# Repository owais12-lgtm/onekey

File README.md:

# One key macropad! 
its a macropad with one key and one encoder powered by a XIAO!

# Features
- Modular Design
- RP2040
- Plug-and-Play
# PCB

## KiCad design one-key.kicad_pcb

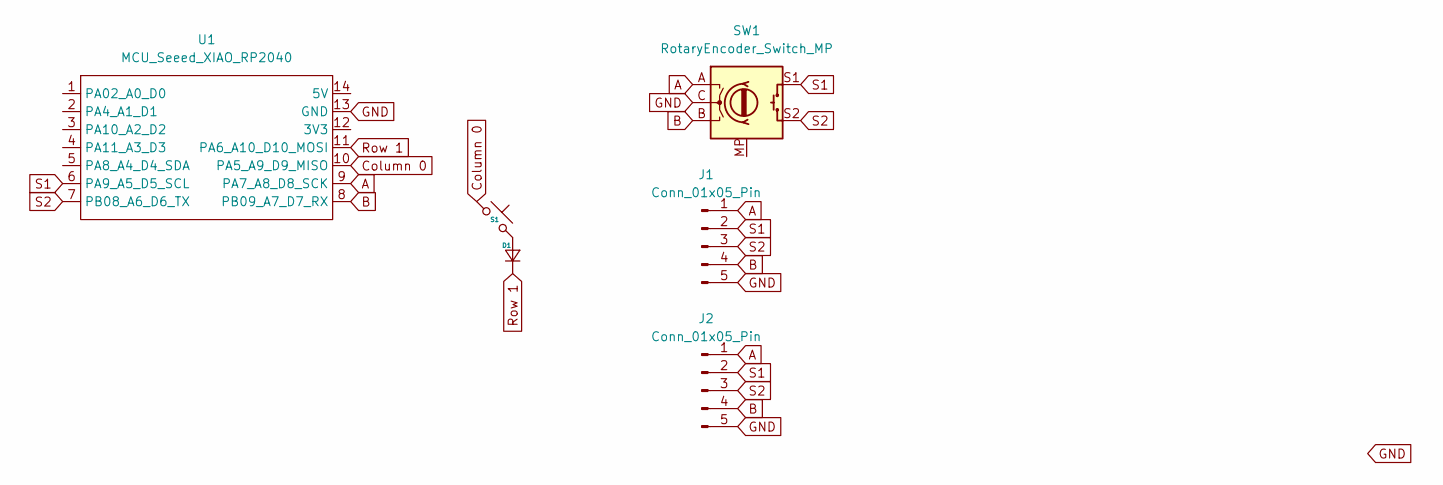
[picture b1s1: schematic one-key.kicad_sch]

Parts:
D1: Diode_DO-35
J1, J2: Conn_01x05_Pin; JST_EH_B5B-EH-A_1x05_P2.50mm_Vertical
S1: MX_PCB_1.00u
SW1: RotaryEncoder_Switch_MP; RotaryEncoder_Alps_EC11E-Switch_Vertical_H20mm
U1: MCU_Seeed_XIAO_RP2040; Seeed_XIAO_RP2040

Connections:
A: J1.1, J2.1, SW1.A, U1.9 (PA7_A8_D8_SCK)
B: J1.4, J2.4, SW1.B, U1.8 (PB09_A7_D7_RX)
Column 0: S1.1, U1.10 (PA5_A9_D9_MISO)
GND: J1.5, J2.5, SW1.C, U1.13 (GND)
unnamed: D1.2 (A), S1.2
Row 1: D1.1 (K), U1.11 (PA6_A10_D10_MOSI)
S1: J1.2, J2.2, SW1.S1, U1.6 (PA9_A5_D5_SCL)
S2: J1.3, J2.3, SW1.S2, U1.7 (PB08_A6_D6_TX)

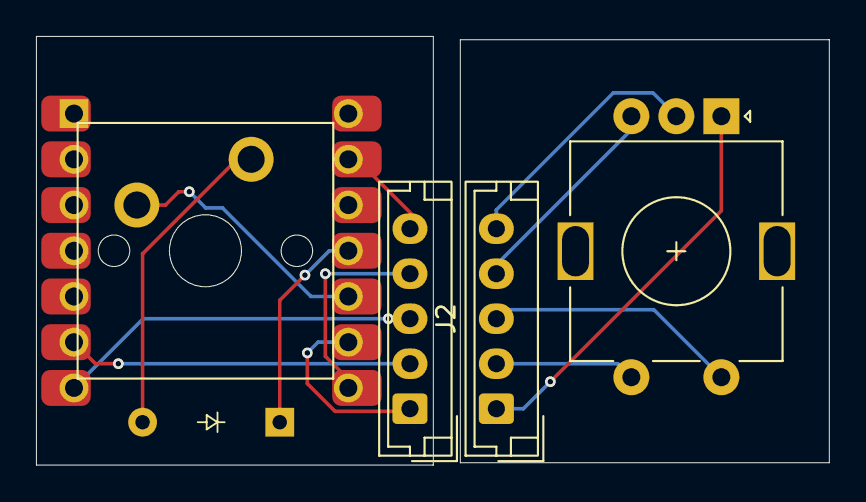
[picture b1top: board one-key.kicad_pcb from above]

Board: 2 copper layers, 44.0 x 23.8 mm, 6 parts (0 on the bottom side), 8 nets.
